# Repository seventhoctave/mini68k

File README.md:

# mini68k

based on http://www.christle.us/index.php?P=4

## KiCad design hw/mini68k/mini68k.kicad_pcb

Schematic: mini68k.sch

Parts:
C1: 100uF; CP_Radial_D5.0mm_P2.50mm
C2: 10uF; CP_Radial_D5.0mm_P2.50mm
C3, C4, C5, C6, C7, C8, C9: .1u; C_Disc_D5.0mm_W2.5mm_P2.50mm
C10: 5pf; C_Disc_D5.0mm_W2.5mm_P2.50mm
C11: 15pf; C_Disc_D5.0mm_W2.5mm_P2.50mm
D1: D_ALT; D_DO-35_SOD27_P10.16mm_Horizontal
D2: RED; LED_D4.0mm
J1: Jack-DC; BarrelJack_Horizontal
J2: 6-bit input port; PinHeader_1x06_P2.54mm_Vertical
J3: 8-bit output port; PinHeader_1x08_P2.54mm_Horizontal
J4: FTDI header COM1; PinHeader_1x06_P2.54mm_Horizontal
J5: FTDI header COM2; PinHeader_1x06_P2.54mm_Horizontal
JP1, JP2: Jumper; PinHeader_1x02_P2.54mm_Vertical
JP3, JP4: Jumper_3_Open; PinHeader_1x03_P2.54mm_Vertical
JP5: Jumper; PinSocket_1x02_P2.54mm_Vertical
R1: 330R; R_Axial_DIN0207_L6.3mm_D2.5mm_P7.62mm_Horizontal
RN1: 1k; R_Array_SIP7
SW1: SW_SPDT; SW_E-Switch_EG1271_DPDT
SW2: SW_Push; SW_PUSH_6mm
U1: HM62256BLP-7; DIP-28_W15.24mm_LongPads
U2: 68008D; DIP-48_W15.24mm_LongPads
U3: L7805; TO-220-3_Horizontal_TabDown
U4: 28C256/27C256; DIP-28_W15.24mm_LongPads
U5: GAL16V8; DIP-20_W7.62mm_LongPads
U6: MAX708CPA+; DIP-8_W7.62mm_LongPads
U7: 68681; DIP-40_W15.24mm_LongPads
U8: 74LS05; DIP-14_W7.62mm_LongPads
X1: 8 Mhz; Oscillator_DIP-14_LargePads
Y1: 3.6864 Mhz; Crystal_HC49-4H_Vertical

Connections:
A0: U1.10, U2.46, U4.10
A1: U1.9, U2.47, U4.9, U7.1
A2: U1.8, U2.48, U4.8, U7.3
A3: U1.7, U2.1, U4.7, U7.5
A4: U1.6, U2.2, U4.6, U7.6
A5: U1.5, U2.3, U4.5
A6: U1.4, U2.4, U4.4
A7: U1.3, U2.5, U4.3
A8: U1.25, U2.6, U4.25
A9: U1.24, U2.7, U4.24
A10: U1.21, U2.8, U4.21
A11: U1.23, U2.9, U4.23
A12: U1.2, U2.10, U4.2
A13: U1.26, U2.11, U4.26
A14: JP3.1 (A), JP4.1 (A), U1.1, U2.12
A15: U2.14, U5.3
A16: U2.16, U5.2
AS: U2.28, U5.4
CLK: JP5.1, U2.34, X1.8
DB0: U1.11, U2.27, U4.11, U7.25
DB1: U1.12, U2.26, U4.12, U7.16
DB2: U1.13, U2.25, U4.13, U7.24
DB3: U1.15, U2.24, U4.15, U7.17
DB4: U1.16, U2.23, U4.16, U7.23
DB5: U1.17, U2.22, U4.17, U7.18
DB6: U1.18, U2.21, U4.18, U7.22
DB7: U1.19, U2.20, U4.19, U7.19
DS: U2.29, U5.5
DTACK: RN1.3 (R2), U2.31, U5.13, U7.9
FC0: U2.45, U5.6
FC1: U2.44, U5.8
FC2: U2.43, U5.9
GND: C1.2, C2.2, C3.2, C4.2, C5.2, C6.2, C7.2, C8.2, C9.2, C10.2, C11.2, J1.2, J1.3, J4.6, J5.6, R1.1, SW2.2, U1.14, U1.20, U2.15, U2.35, U3.2, U4.14, U4.20, U5.10, U5.11, U6.3, U6.4, U7.20, U8.7, X1.7
HALT: U2.36, U5.12
IACK: U5.18, U7.37
INTR: RN1.5 (R4), U2.41, U7.21
IP0: J2.1, U7.7
IP1: J2.2, U7.4
IP2: J2.3, U7.36
IP3: J2.4, U7.2
IP4: J2.5, U7.39
IP5: J2.6, U7.38
MR: SW2.1, U6.1
unnamed: C1.1, SW1.1, U3.1
unnamed: D1.1 (K), SW1.2
unnamed: D1.2 (A), J1.1
unnamed: D2.1 (K), R1.2
unnamed: J4.4, JP1.1
unnamed: J5.4, JP2.1
unnamed: U6.8, U8.1
OP0: J3.1, U7.29
OP1: J3.2, U7.12
OP2: J3.3, U7.28
OP3: J3.4, U7.13
OP4: J3.5, U7.27
OP5: J3.6, U7.14
OP6: J3.7, U7.26
OP7: J3.8, U7.15
R/W: U2.30, U5.7, U7.8
RAM_OE: U1.22, U5.16
RAM_WE: U1.27, U5.15
RESET: RN1.4 (R3), U2.37, U5.17, U7.34
ROM_OE: U4.22, U5.14
ROM_PIN1: JP3.2 (C), U4.1
ROM_PIN27: JP4.2 (C), U4.27
RST: RN1.2 (R1), U5.1, U8.2
RX1: J4.3, U7.31
RX2: J5.3, U7.10
TX1: J4.2, U7.30
TX2: J5.2, U7.11
UART_CS: U5.19, U7.35
VCC: C2.1, C3.1, C4.1, C5.1, C6.1, C7.1, C8.1, C9.1, D2.2 (A), JP1.2, JP2.2, JP3.3 (B), JP4.3 (B), RN1.1 (common), U1.28, U2.13, U2.33, U2.39, U2.40, U2.42, U3.3, U4.28, U5.20, U6.2, U7.40, U8.14, X1.14
X1: C10.1, JP5.2, U7.32, Y1.1
X2: C11.1, U7.33, Y1.2

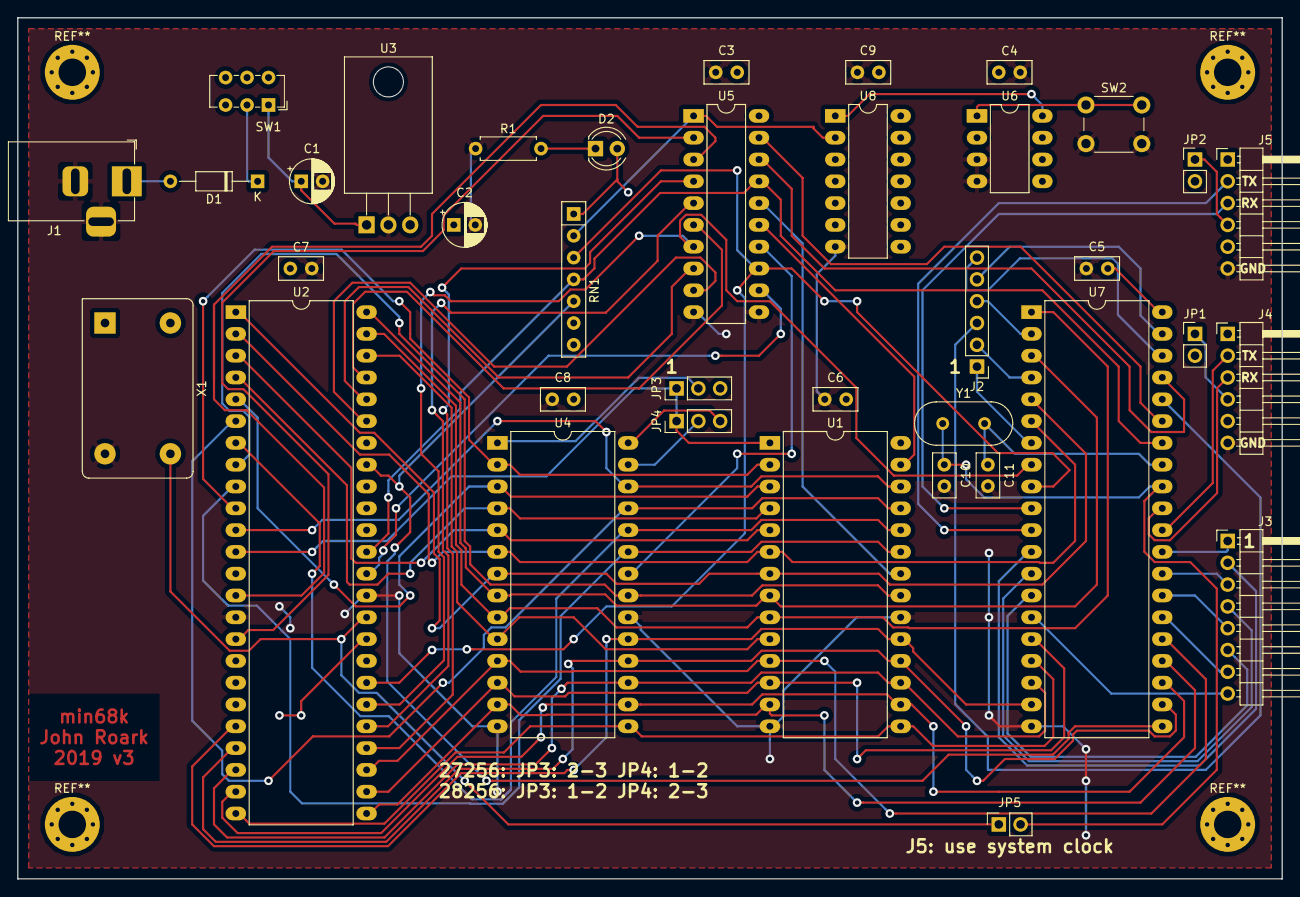
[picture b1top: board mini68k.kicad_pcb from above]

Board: 2 copper layers, 147.3 x 100.3 mm, 37 parts (0 on the bottom side), 74 nets.

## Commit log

2018-06-12 "port" of Mike Christle's mini68k bios to gasm
2018-06-12 URL to original
2018-06-13 print hex, dump mem, fill mem
2018-06-13 bug in parsing params for dump mem
2018-06-14 add line feed to strings
2018-06-19 * intial checkin of kicad schematics
2018-06-20 * oscillator, gal
2018-06-20 everything but reset and i/o
2018-06-20 picture of breadboard version
2018-06-22 initial pcb layout
2018-06-22 initial layout
2018-06-22 routing complete
2018-06-23 3d model
2018-06-23 re-pour planes
2018-06-28 v2 fixes:
    - swapped rx/tx
    - reset switch
    - pullup RST
    - pin one of X1
    - remove VCC plane from under 7805
2019-03-03 gal pld
2019-03-10 KiCad 5
2019-03-10 update footprints, expose i/o from 68681
2019-03-11 run drc and fix issues
2019-03-11 better fills
2019-03-11 more updated footprints and 3d
2019-03-11 better 3d
2019-03-13 jumpers for 27256/28256
2019-03-13 labels
2019-03-15 update symbols
2019-03-15 correct ram pinout... update symbols
2019-03-15 galasm format pld
2019-03-17 seperate crystal for DUART
2019-03-17 v1 pcb photo
2019-09-25 backup
2020-07-29 100x100 pcb image
